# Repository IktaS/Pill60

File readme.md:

This is Pill 60, it offers various bottom row layout, a stepped caps, an OLED screen, and two rotary encoder, and uses Kailh Hotswap Socket, and underglow RGB LED.

layout is [this](http://www.keyboard-layout-editor.com/##@_name=Pill60&author=IktaS%3B&@_a:7&f:7%3B&=1&=1&=1&=1&=1&=1&=1&=1&=1&=1&=1&=1&=1&_c=%2300ffdd%3B&=1&=1%3B&@_c=%23cccccc&w:1.5%3B&=1.5&=1&=1&=1&=1&=1&=1&=1&=1&=1&=1&=1&=1&_c=%2300cc55&w:1.5%3B&=1.5%3B&@_c=%2350d38a&w:1.75%3B&=1.75&_c=%23cccccc%3B&=1&=1&=1&=1&=1&=1&=1&=1&=1&=1&=1&_c=%2300cc55&w:2.25%3B&=2.25%3B&@_c=%23aaaacc&w:2.25%3B&=2.25&_c=%23cccccc%3B&=1&=1&=1&=1&=1&=1&=1&=1&=1&=1&_c=%23cc77cc&w:1.75%3B&=1.75&=1%3B&@_c=%23995555&w:1.25%3B&=1.25&_w:1.25%3B&=1.25&_w:1.25%3B&=1.25&_c=%23889988&w:6.25%3B&=6.25&_c=%23558899&w:1.25%3B&=1.25&_w:1.25%3B&=1.25&_w:1.25%3B&=1.25&_w:1.25%3B&=1.25%3B&@_c=%23b3ce29&w:1.5%3B&=1.5&=1&_w:1.5%3B&=1.5&_c=%23939393&w:6%3B&=6&_c=%23558899&w:1.5%3B&=1.5&=1&=1&_w:1.5%3B&=1.5&_x:0.5&c=%2350d38a&w:1.25&w2:1.75&l:true%3B&=1.75)

This 60% keyboard that uses BluePill or STM32F103C8T6.This is my first board, Any feedback is appreciated. Contact me on Discord Ikta#8871.

## Firmware
Firmware is currently waiting for merge to QMK Firmware Repository, but you can still access it from my [fork](https://github.com/IktaS/qmk_firmware/tree/pill60/keyboards/handwired/pill60)

## Update
Modified the pinout diagram so that it doesn't crash with Black Pill or STM32F4xxx line of board, the pinout obviously will be different, but because all uses the a valid pin even with Black Pill / Blue Pill configuration, pin matrix diagram can be modified in firmware level.

## Caution
You might need to use a jumper for a more reliable connector in the caps/control key. I guess the pad is a bit too small for it to keep holding on with constant pressure of being pressed hard.

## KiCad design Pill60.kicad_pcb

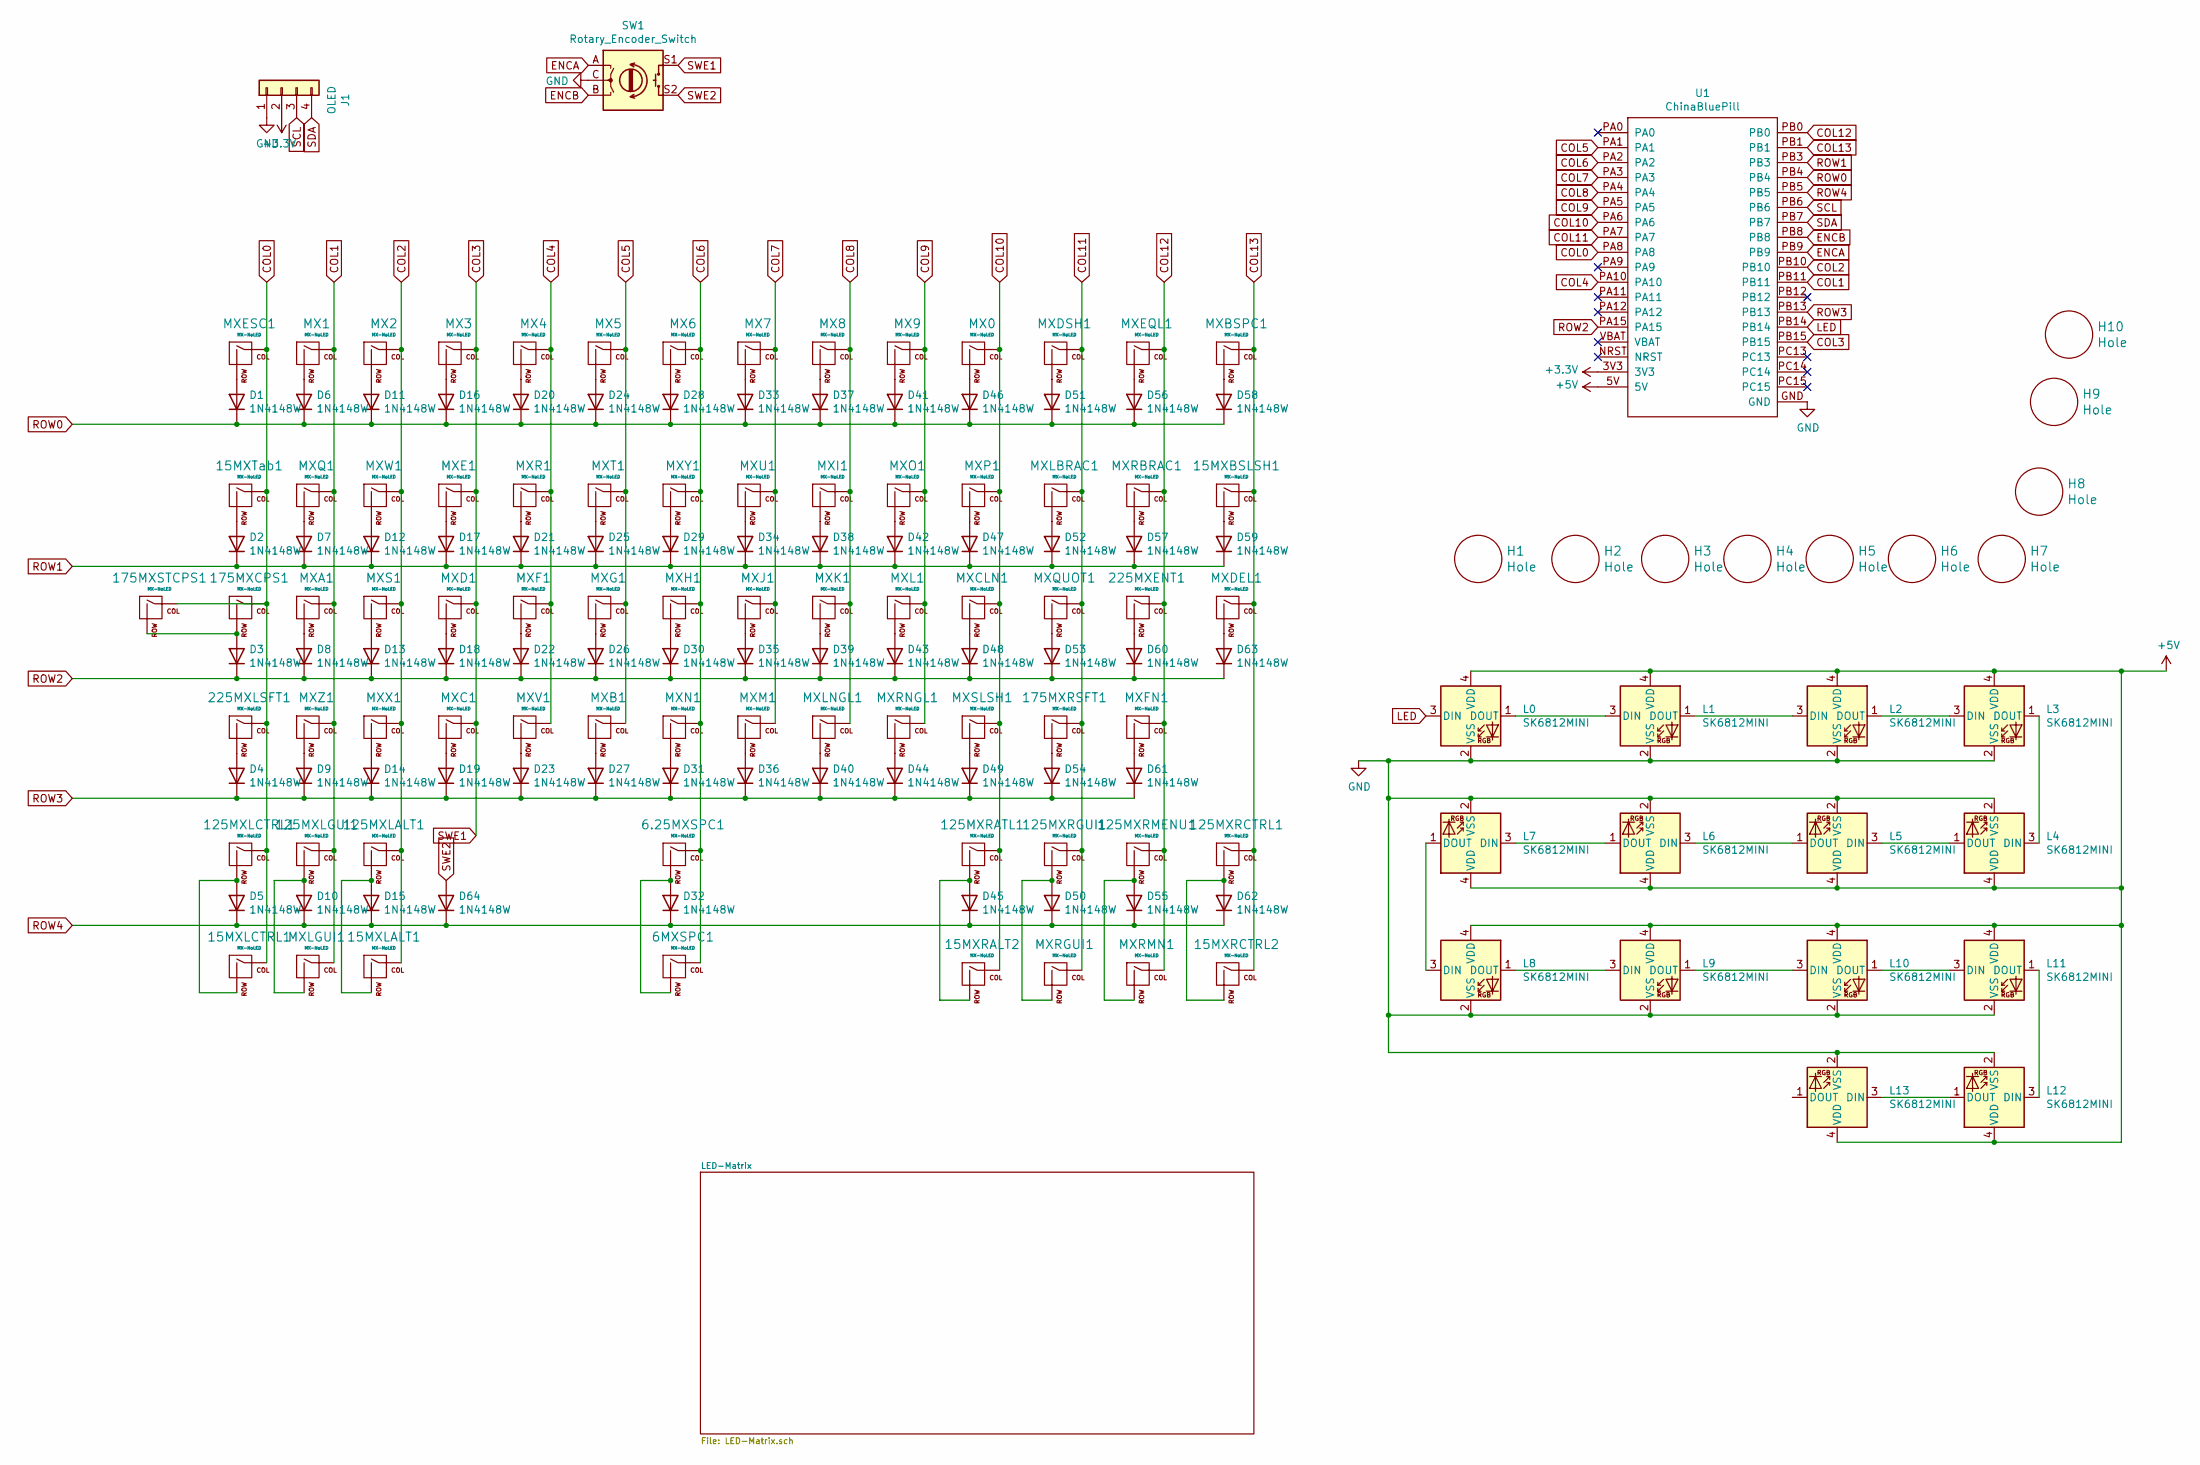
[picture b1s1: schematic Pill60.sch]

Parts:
6.25MXSPC1: MX-NoLED; MXOnly-6.25U-Hotswap-ReversedStabilizers-AntiShear
6MXSPC1: MX-NoLED; MXOnly-6U-ReversedStabilizers-NoLED-HotSwap-AntiShear
15MXBSLSH1, 15MXLALT1, 15MXLCTRL1, 15MXRALT2, 15MXRCTRL2, 15MXTab1: MX-NoLED; MXOnly-1.5U-Hotswap-AntiShear
125MXLALT1, 125MXLCTRL1, 125MXLGUI1, 125MXRATL1, 125MXRCTRL1, 125MXRGUI1, 125MXRMENU1: MX-NoLED; MXOnly-1.25U-Hotswap-AntiShear
175MXCPS1: MX-NoLED; MXOnly-1.75U-NoLED
175MXRSFT1: MX-NoLED; MXOnly-1.75U-Hotswap-AntiShear
175MXSTCPS1: MX-NoLED; MXOnly-1U-NoLED
225MXENT1, 225MXLSFT1: MX-NoLED; MXOnly-2.25U-Hotswap-AntiShear
D1, D2, D3, D4, D5, D6, D7, D8, D9, D10, D11, D12, D13, D14, D15, D16, D17, D18, D19, D20, D21, D22, D23, D24, D25, D26, D27, D28, D29, D30, D31, D32, D33, D34, D35, D36, D37, D38, D39, D40, D41, D42, D43, D44, D45, D46, D47, D48, D49, D50, D51, D52, D53, D54, D55, D56, D57, D58, D59, D60, D61, D62, D63, D64: 1N4148W; D_SOD-123
H1, H2, H3, H4, H5, H6, H7, H8, H9, H10: Hole; MountingHole_2.2mm_M2
J1: OLED; PinSocket_1x04_P2.54mm_Vertical
L0, L1, L2, L3, L4, L5, L6, L7, L8, L9, L10, L11, L12, L13: SK6812MINI; LED_SK6812MINI_PLCC4_3.5x3.5mm_P1.75mm
MX0, MX1, MX2, MX3, MX4, MX5, MX6, MX7, MX8, MX9: MX-NoLED; MXOnly-1U-Hotswap-Antishear
MXA1: MX-NoLED; MXOnly-1U-Hotswap-Antishear
MXB1: MX-NoLED; MXOnly-1U-Hotswap-Antishear
MXBSPC1: MX-NoLED; MXOnly-1U-Hotswap-Antishear
MXC1: MX-NoLED; MXOnly-1U-Hotswap-Antishear
MXCLN1: MX-NoLED; MXOnly-1U-Hotswap-Antishear
MXD1: MX-NoLED; MXOnly-1U-Hotswap-Antishear
MXDEL1: MX-NoLED; MXOnly-1U-Hotswap-Antishear
MXDSH1: MX-NoLED; MXOnly-1U-Hotswap-Antishear
MXE1: MX-NoLED; MXOnly-1U-Hotswap-Antishear
MXEQL1: MX-NoLED; MXOnly-1U-Hotswap-Antishear
MXESC1: MX-NoLED; MXOnly-1U-Hotswap-Antishear
MXF1: MX-NoLED; MXOnly-1U-Hotswap-Antishear
MXFN1: MX-NoLED; MXOnly-1U-Hotswap-Antishear
MXG1: MX-NoLED; MXOnly-1U-Hotswap-Antishear
MXH1: MX-NoLED; MXOnly-1U-Hotswap-Antishear
MXI1: MX-NoLED; MXOnly-1U-Hotswap-Antishear
MXJ1: MX-NoLED; MXOnly-1U-Hotswap-Antishear
MXK1: MX-NoLED; MXOnly-1U-Hotswap-Antishear
MXL1: MX-NoLED; MXOnly-1U-Hotswap-Antishear
MXLBRAC1: MX-NoLED; MXOnly-1U-Hotswap-Antishear
MXLGUI1: MX-NoLED; MXOnly-1U-Hotswap-Antishear
MXLNGL1: MX-NoLED; MXOnly-1U-Hotswap-Antishear
MXM1: MX-NoLED; MXOnly-1U-Hotswap-Antishear
MXN1: MX-NoLED; MXOnly-1U-Hotswap-Antishear
MXO1: MX-NoLED; MXOnly-1U-Hotswap-Antishear
MXP1: MX-NoLED; MXOnly-1U-Hotswap-Antishear
MXQ1: MX-NoLED; MXOnly-1U-Hotswap-Antishear
MXQUOT1: MX-NoLED; MXOnly-1U-Hotswap-Antishear
MXR1: MX-NoLED; MXOnly-1U-Hotswap-Antishear
MXRBRAC1: MX-NoLED; MXOnly-1U-Hotswap-Antishear
MXRGUI1: MX-NoLED; MXOnly-1U-Hotswap-Antishear
MXRMN1: MX-NoLED; MXOnly-1U-Hotswap-Antishear
MXRNGL1: MX-NoLED; MXOnly-1U-Hotswap-Antishear
MXS1: MX-NoLED; MXOnly-1U-Hotswap-Antishear
MXSLSH1: MX-NoLED; MXOnly-1U-Hotswap-Antishear
MXT1: MX-NoLED; MXOnly-1U-Hotswap-Antishear
MXU1: MX-NoLED; MXOnly-1U-Hotswap-Antishear
MXV1: MX-NoLED; MXOnly-1U-Hotswap-Antishear
MXW1: MX-NoLED; MXOnly-1U-Hotswap-Antishear
MXX1: MX-NoLED; MXOnly-1U-Hotswap-Antishear
MXY1: MX-NoLED; MXOnly-1U-Hotswap-Antishear
MXZ1: MX-NoLED; MXOnly-1U-Hotswap-Antishear
SW1: Rotary_Encoder_Switch; RotaryEncoder_Alps_EC11E-Switch_Vertical_H20mm
U1: ChinaBluePill; ChinaBluePill_SneakyFootprint

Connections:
+3V3: J1.2, U1.3V3
+5V: L0.4 (VDD), L1.4 (VDD), L2.4 (VDD), L3.4 (VDD), L4.4 (VDD), L5.4 (VDD), L6.4 (VDD), L7.4 (VDD), L8.4 (VDD), L9.4 (VDD), L10.4 (VDD), L11.4 (VDD), L12.4 (VDD), L13.4 (VDD), U1.5V
COL0: 15MXLCTRL1.1 (COL), 15MXTab1.1 (COL), 125MXLCTRL1.1 (COL), 175MXCPS1.1 (COL), 175MXSTCPS1.1 (COL), 225MXLSFT1.1 (COL), MXESC1.1 (COL), U1.PA8
COL1: 125MXLGUI1.1 (COL), MX1.1 (COL), MXA1.1 (COL), MXLGUI1.1 (COL), MXQ1.1 (COL), MXZ1.1 (COL), U1.PB11
COL2: 15MXLALT1.1 (COL), 125MXLALT1.1 (COL), MX2.1 (COL), MXS1.1 (COL), MXW1.1 (COL), MXX1.1 (COL), U1.PB10
COL3: MX3.1 (COL), MXC1.1 (COL), MXD1.1 (COL), MXE1.1 (COL), SW1.S1, U1.PB15
COL4: MX4.1 (COL), MXF1.1 (COL), MXR1.1 (COL), MXV1.1 (COL), U1.PA10
COL5: MX5.1 (COL), MXB1.1 (COL), MXG1.1 (COL), MXT1.1 (COL), U1.PA1
COL6: 6.25MXSPC1.1 (COL), 6MXSPC1.1 (COL), MX6.1 (COL), MXH1.1 (COL), MXN1.1 (COL), MXY1.1 (COL), U1.PA2
COL7: MX7.1 (COL), MXJ1.1 (COL), MXM1.1 (COL), MXU1.1 (COL), U1.PA3
COL8: MX8.1 (COL), MXI1.1 (COL), MXK1.1 (COL), MXLNGL1.1 (COL), U1.PA4
COL9: MX9.1 (COL), MXL1.1 (COL), MXO1.1 (COL), MXRNGL1.1 (COL), U1.PA5
COL10: 15MXRALT2.1 (COL), 125MXRATL1.1 (COL), MX0.1 (COL), MXCLN1.1 (COL), MXP1.1 (COL), MXSLSH1.1 (COL), U1.PA6
COL11: 125MXRGUI1.1 (COL), 175MXRSFT1.1 (COL), MXDSH1.1 (COL), MXLBRAC1.1 (COL), MXQUOT1.1 (COL), MXRGUI1.1 (COL), U1.PA7
COL12: 125MXRMENU1.1 (COL), 225MXENT1.1 (COL), MXEQL1.1 (COL), MXFN1.1 (COL), MXRBRAC1.1 (COL), MXRMN1.1 (COL), U1.PB0
COL13: 15MXBSLSH1.1 (COL), 15MXRCTRL2.1 (COL), 125MXRCTRL1.1 (COL), MXBSPC1.1 (COL), MXDEL1.1 (COL), U1.PB1
ENCA: SW1.A, U1.PB9
ENCB: SW1.B, U1.PB8
GND: J1.1, L0.2 (VSS), L1.2 (VSS), L2.2 (VSS), L3.2 (VSS), L4.2 (VSS), L5.2 (VSS), L6.2 (VSS), L7.2 (VSS), L8.2 (VSS), L9.2 (VSS), L10.2 (VSS), L11.2 (VSS), L12.2 (VSS), L13.2 (VSS), SW1.C, U1.GND
LED: L0.3 (DIN), U1.PB14
unnamed: 6.25MXSPC1.2 (ROW), 6MXSPC1.2 (ROW), D32.2 (A)
unnamed: 15MXBSLSH1.2 (ROW), D59.2 (A)
unnamed: 15MXTab1.2 (ROW), D2.2 (A)
unnamed: 15MXLALT1.2 (ROW), 125MXLALT1.2 (ROW), D15.2 (A)
unnamed: 15MXLCTRL1.2 (ROW), 125MXLCTRL1.2 (ROW), D5.2 (A)
unnamed: 125MXLGUI1.2 (ROW), D10.2 (A), MXLGUI1.2 (ROW)
unnamed: 15MXRALT2.2 (ROW), 125MXRATL1.2 (ROW), D45.2 (A)
unnamed: 15MXRCTRL2.2 (ROW), 125MXRCTRL1.2 (ROW), D62.2 (A)
unnamed: 125MXRGUI1.2 (ROW), D50.2 (A), MXRGUI1.2 (ROW)
unnamed: 125MXRMENU1.2 (ROW), D55.2 (A), MXRMN1.2 (ROW)
unnamed: 175MXCPS1.2 (ROW), 175MXSTCPS1.2 (ROW), D3.2 (A)
unnamed: 175MXRSFT1.2 (ROW), D54.2 (A)
unnamed: 225MXENT1.2 (ROW), D60.2 (A)
unnamed: 225MXLSFT1.2 (ROW), D4.2 (A)
unnamed: D1.2 (A), MXESC1.2 (ROW)
unnamed: D6.2 (A), MX1.2 (ROW)
unnamed: D7.2 (A), MXQ1.2 (ROW)
unnamed: D8.2 (A), MXA1.2 (ROW)
unnamed: D9.2 (A), MXZ1.2 (ROW)
unnamed: D11.2 (A), MX2.2 (ROW)
unnamed: D12.2 (A), MXW1.2 (ROW)
unnamed: D13.2 (A), MXS1.2 (ROW)
unnamed: D14.2 (A), MXX1.2 (ROW)
unnamed: D16.2 (A), MX3.2 (ROW)
unnamed: D17.2 (A), MXE1.2 (ROW)
unnamed: D18.2 (A), MXD1.2 (ROW)
unnamed: D19.2 (A), MXC1.2 (ROW)
unnamed: D20.2 (A), MX4.2 (ROW)
unnamed: D21.2 (A), MXR1.2 (ROW)
unnamed: D22.2 (A), MXF1.2 (ROW)
unnamed: D23.2 (A), MXV1.2 (ROW)
unnamed: D24.2 (A), MX5.2 (ROW)
unnamed: D25.2 (A), MXT1.2 (ROW)
unnamed: D26.2 (A), MXG1.2 (ROW)
unnamed: D27.2 (A), MXB1.2 (ROW)
unnamed: D28.2 (A), MX6.2 (ROW)
unnamed: D29.2 (A), MXY1.2 (ROW)
unnamed: D30.2 (A), MXH1.2 (ROW)
unnamed: D31.2 (A), MXN1.2 (ROW)
unnamed: D33.2 (A), MX7.2 (ROW)
unnamed: D34.2 (A), MXU1.2 (ROW)
unnamed: D35.2 (A), MXJ1.2 (ROW)
unnamed: D36.2 (A), MXM1.2 (ROW)
unnamed: D37.2 (A), MX8.2 (ROW)
unnamed: D38.2 (A), MXI1.2 (ROW)
unnamed: D39.2 (A), MXK1.2 (ROW)
unnamed: D40.2 (A), MXLNGL1.2 (ROW)
unnamed: D41.2 (A), MX9.2 (ROW)
unnamed: D42.2 (A), MXO1.2 (ROW)
unnamed: D43.2 (A), MXL1.2 (ROW)
unnamed: D44.2 (A), MXRNGL1.2 (ROW)
unnamed: D46.2 (A), MX0.2 (ROW)
unnamed: D47.2 (A), MXP1.2 (ROW)
unnamed: D48.2 (A), MXCLN1.2 (ROW)
unnamed: D49.2 (A), MXSLSH1.2 (ROW)
unnamed: D51.2 (A), MXDSH1.2 (ROW)
unnamed: D52.2 (A), MXLBRAC1.2 (ROW)
unnamed: D53.2 (A), MXQUOT1.2 (ROW)
unnamed: D56.2 (A), MXEQL1.2 (ROW)
unnamed: D57.2 (A), MXRBRAC1.2 (ROW)
unnamed: D58.2 (A), MXBSPC1.2 (ROW)
unnamed: D61.2 (A), MXFN1.2 (ROW)
unnamed: D63.2 (A), MXDEL1.2 (ROW)
unnamed: L0.1 (DOUT), L1.3 (DIN)
unnamed: L1.1 (DOUT), L2.3 (DIN)
unnamed: L2.1 (DOUT), L3.3 (DIN)
unnamed: L3.1 (DOUT), L4.3 (DIN)
unnamed: L4.1 (DOUT), L5.3 (DIN)
unnamed: L5.1 (DOUT), L6.3 (DIN)
unnamed: L6.1 (DOUT), L7.3 (DIN)
unnamed: L7.1 (DOUT), L8.3 (DIN)
unnamed: L8.1 (DOUT), L9.3 (DIN)
unnamed: L10.1 (DOUT), L11.3 (DIN)
unnamed: L9.1 (DOUT), L10.3 (DIN)
unnamed: L11.1 (DOUT), L12.3 (DIN)
unnamed: L12.1 (DOUT), L13.3 (DIN)
ROW0: D1.1 (K), D6.1 (K), D11.1 (K), D16.1 (K), D20.1 (K), D24.1 (K), D28.1 (K), D33.1 (K), D37.1 (K), D41.1 (K), D46.1 (K), D51.1 (K), D56.1 (K), D58.1 (K), U1.PB4
ROW1: D2.1 (K), D7.1 (K), D12.1 (K), D17.1 (K), D21.1 (K), D25.1 (K), D29.1 (K), D34.1 (K), D38.1 (K), D42.1 (K), D47.1 (K), D52.1 (K), D57.1 (K), D59.1 (K), U1.PB3
ROW2: D3.1 (K), D8.1 (K), D13.1 (K), D18.1 (K), D22.1 (K), D26.1 (K), D30.1 (K), D35.1 (K), D39.1 (K), D43.1 (K), D48.1 (K), D53.1 (K), D60.1 (K), D63.1 (K), U1.PA15
ROW3: D4.1 (K), D9.1 (K), D14.1 (K), D19.1 (K), D23.1 (K), D27.1 (K), D31.1 (K), D36.1 (K), D40.1 (K), D44.1 (K), D49.1 (K), D54.1 (K), D61.1 (K), U1.PB13
ROW4: D5.1 (K), D10.1 (K), D15.1 (K), D32.1 (K), D45.1 (K), D50.1 (K), D55.1 (K), D62.1 (K), D64.1 (K), U1.PB5
SCL: J1.3, U1.PB6
SDA: J1.4, U1.PB7
SWE2: D64.2 (A), SW1.S2

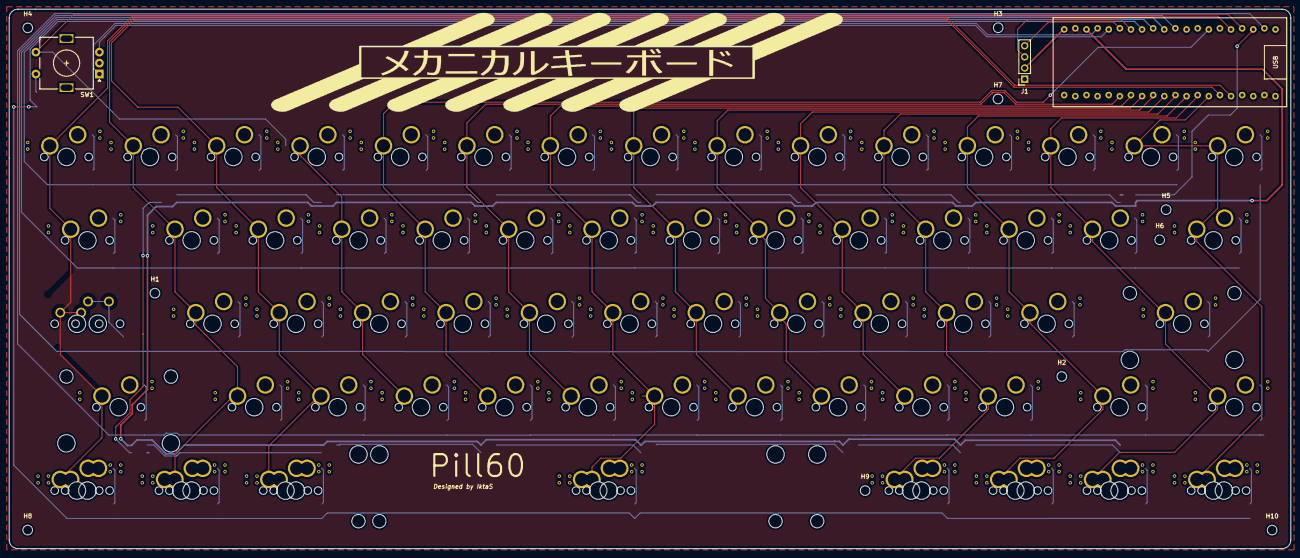
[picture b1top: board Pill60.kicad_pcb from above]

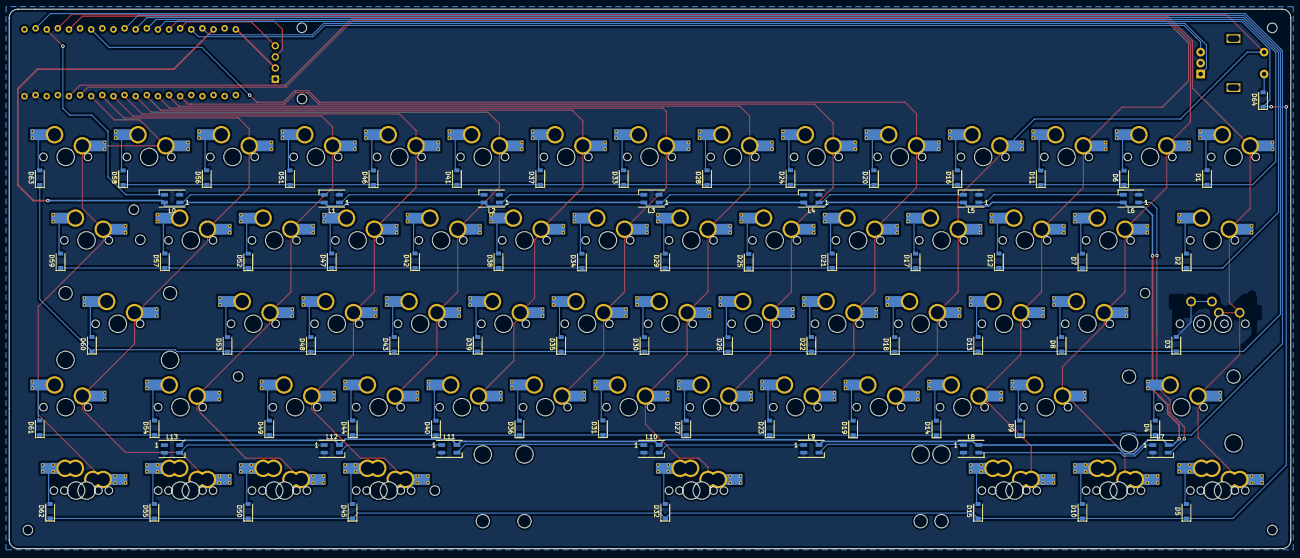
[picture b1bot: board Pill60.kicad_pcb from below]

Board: 2 copper layers, 292.7 x 123.2 mm, 163 parts (78 on the bottom side), 104 nets.

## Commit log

2020-08-18 plates
2020-08-18 readme
2020-08-18 reference southwest mat
2020-08-18 reference ai03 done
2020-08-19 submodules
2020-08-19 add lib
2020-08-19 move readme
2020-08-19 hard pivot
2020-08-19 pivot MCU
2020-08-19 remove submodule
2020-08-19 cleaningup
2020-08-19 cleanup
2020-08-20 done wiring etc
2020-08-20 gerber
2020-08-20 deleted stuff
2020-08-20 images and readme
2020-08-20 More images
2020-08-20 add underglow
2020-08-20 fix stupid mistakes
2020-08-20 underglow
2020-08-20 change images
2020-08-21 connecting some grounds
2020-08-21 Fix wires and make stuff better
2020-08-21 Gerbers v1.1.1
2020-08-21 Gerbers
2020-08-21 readme and images
2020-08-21 Better wires
2020-08-21 fixed stupid mistake
2020-08-21 added more holes for plate and pcb mounting
2020-08-22 Gerber for latest version
2020-08-22 Images for latest version
2020-08-22 readme and images update
2020-08-22 Sneaky footprint
    offset pin holes for bluepill, might or might not work
2020-08-22 images and gerber
2020-08-22 added support for blackpill
2020-08-24 changed pin diagram to avoid bad pin
2020-08-24 Images and gerbers
2020-08-29 create reference in plate file
2020-10-30 update readme and add case files
2021-03-10 Add caution in readme
2021-05-22 add acrylic case files
